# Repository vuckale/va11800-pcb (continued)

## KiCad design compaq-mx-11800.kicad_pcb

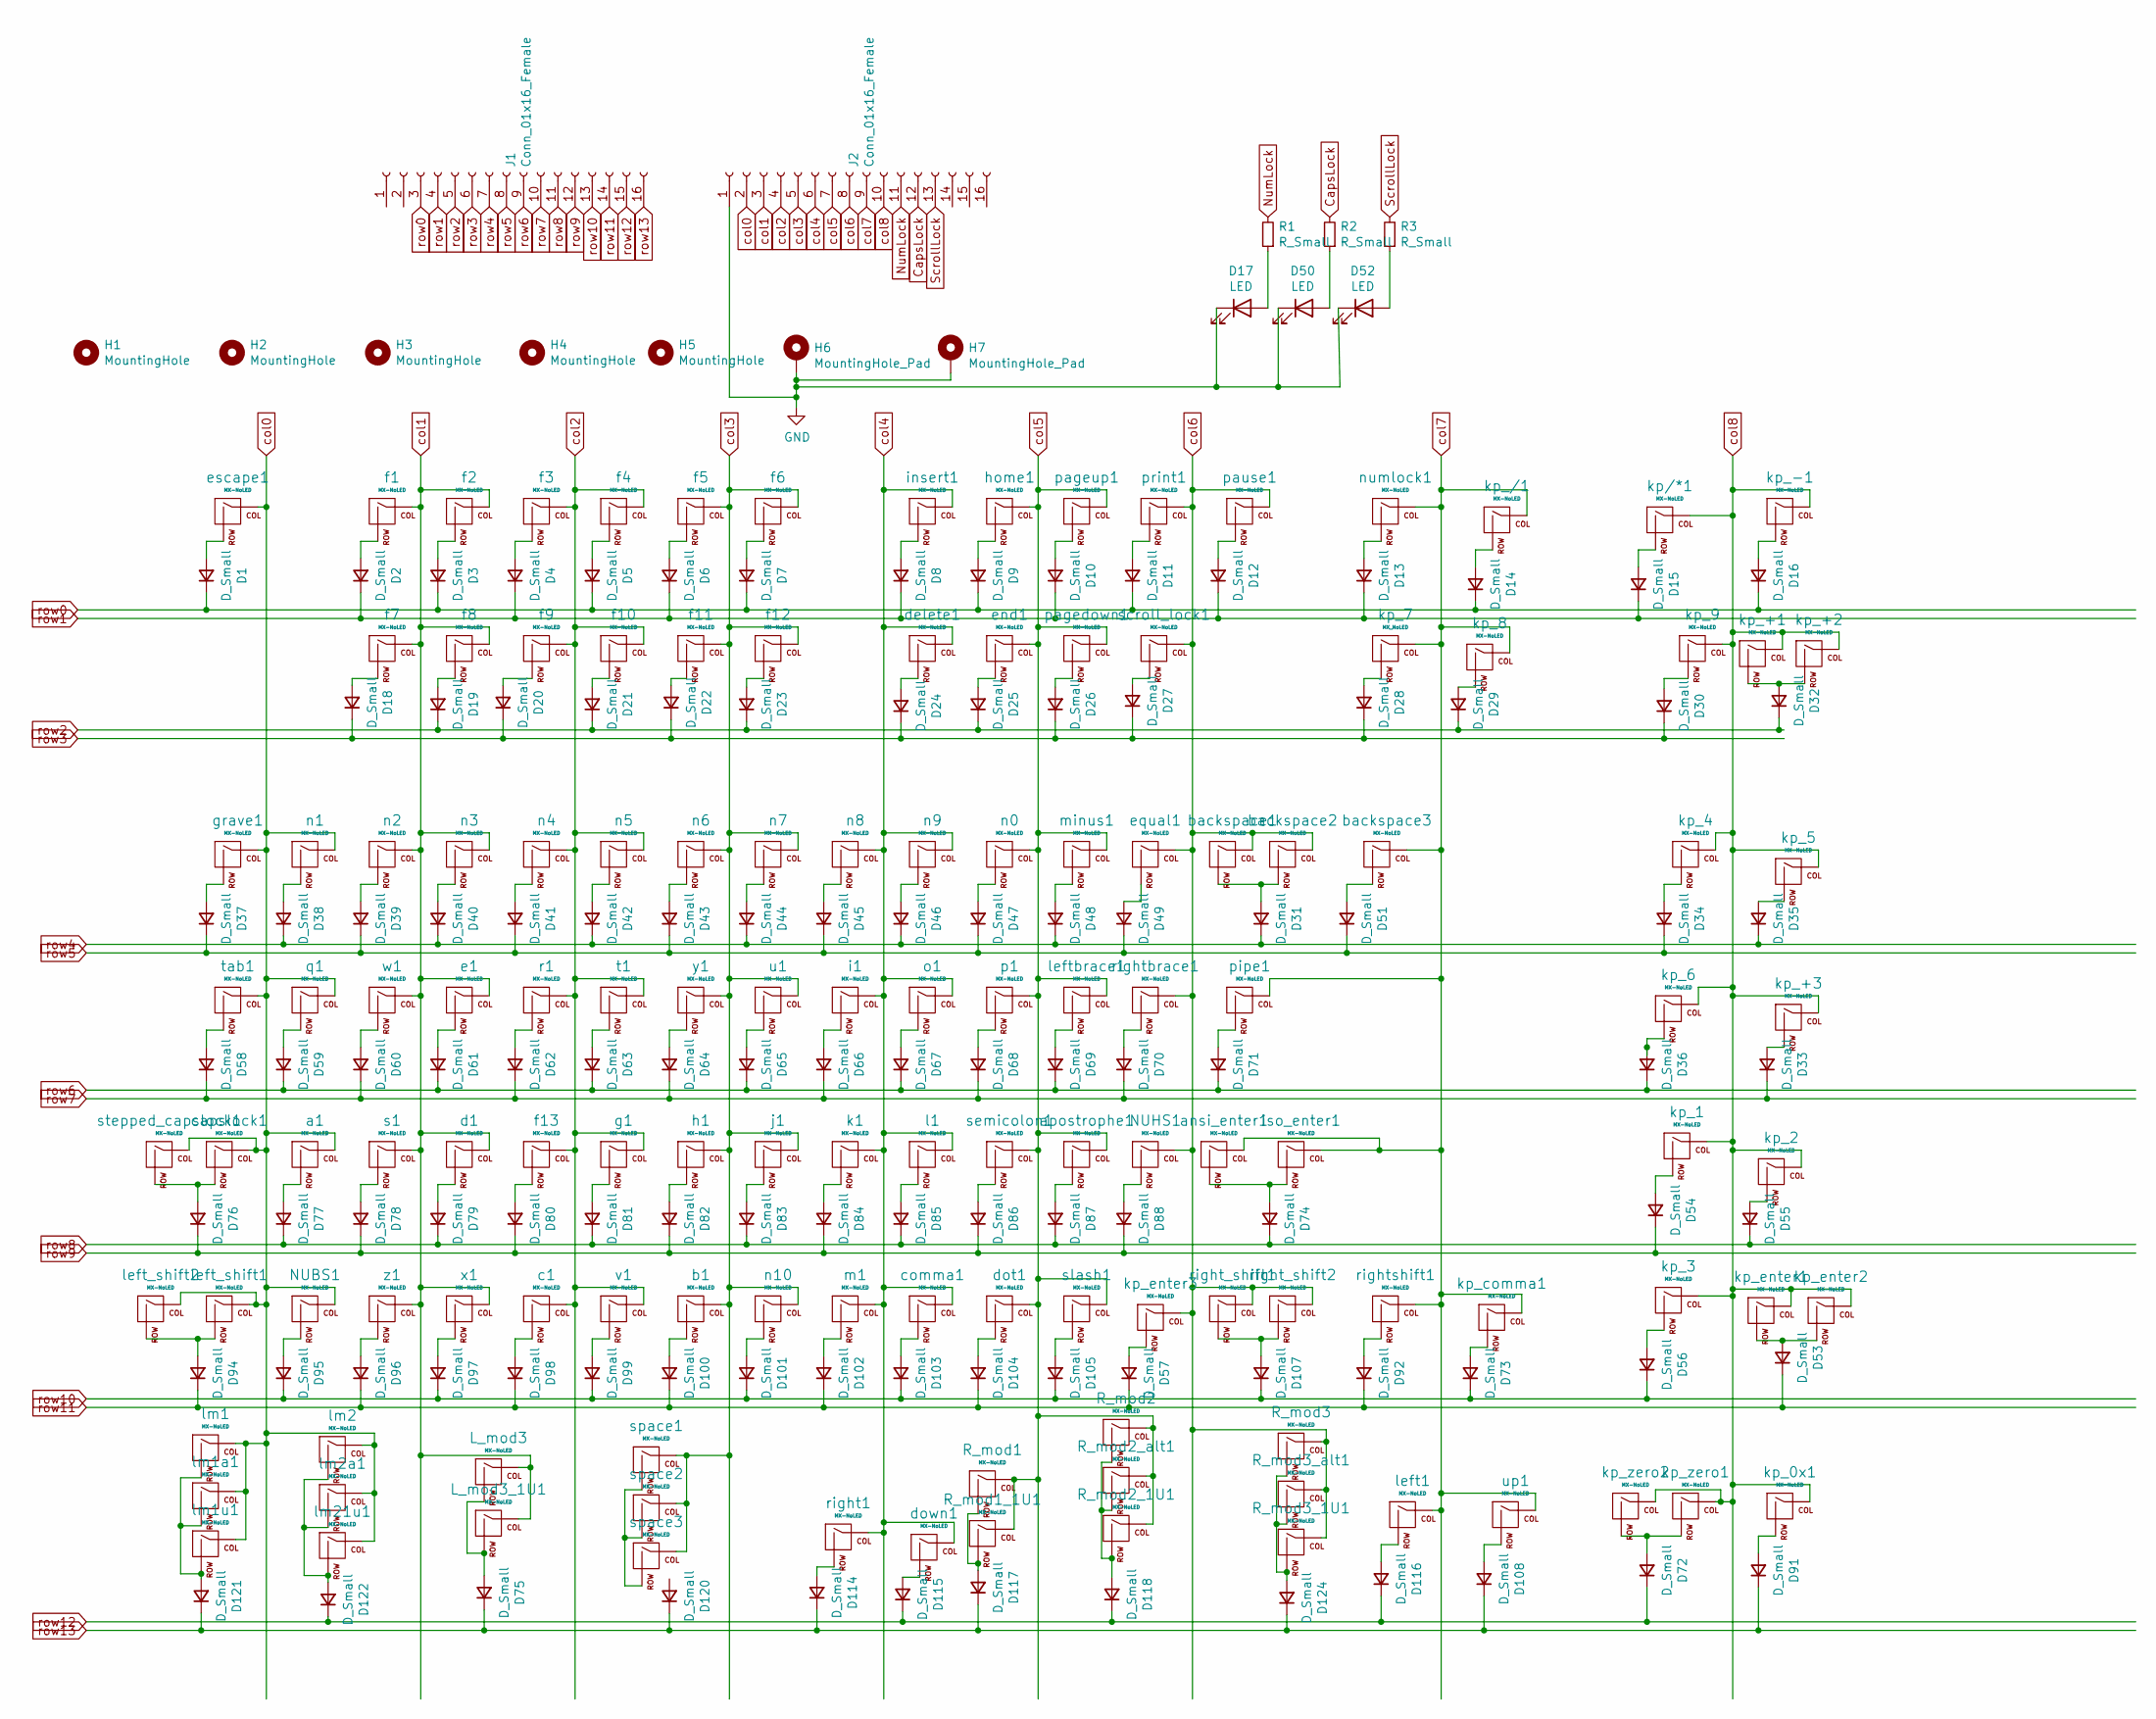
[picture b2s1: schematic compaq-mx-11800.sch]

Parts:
D1: D_Small; Diode-dual
D2, D3, D4, D5, D6, D7, D8, D9, D10, D11, D12, D13, D14, D15, D16, D18, D19, D20, D21, D22, D23, D24, D25, D26, D27, D28, D29, D30, D31, D32, D33, D34, D35, D36, D37, D38, D39, D40, D41, D42, D43, D44, D45, D46, D47, D48, D49, D51, D53, D54, D55, D56, D57, D58, D59, D60, D61, D62, D63, D64, D65, D66, D67, D68, D69, D70, D71, D72, D73, D74, D75, D76, D77, D78, D79, D80, D81, D82, D83, D84, D85, D86, D87, D88, D91, D92, D94, D95, D96, D97, D98, D99, D100, D101, D102, D103, D104, D105, D107, D108, D114, D115, D116, D117, D118, D120, D121, D122, D124: D_Small; Diode
D17, D50, D52: LED; LED_D2.00mm
H1, H2, H3, H4, H5: MountingHole; MountingHole_3.2mm_M3
H6, H7: MountingHole_Pad; SolidCopper
J1, J2: Conn_01x16_Female; PinHeader_1x16_P2.54mm_Vertical
L_mod3: MX-NoLED; MXOnly-1.25U-NoLED
L_mod3_1U1: MX-NoLED; MXOnly-1U-NoLED
NUBS1: MX-NoLED; MXOnly-1U-NoLED
NUHS1: MX-NoLED; MXOnly-1U-NoLED
R1, R2, R3: R_Small; Resistor
R_mod1, R_mod2_alt1, R_mod3_alt1: MX-NoLED; MXOnly-1.25U-NoLED
R_mod1_1U1, R_mod2_1U1, R_mod3_1U1: MX-NoLED; MXOnly-1U-NoLED
R_mod2, R_mod3: MX-NoLED; MXOnly-1.5U-NoLED
a1: MX-NoLED; MXOnly-1U-NoLED
ansi_enter1: MX-NoLED; MXOnly-2.25U-NoLED
apostrophe1: MX-NoLED; MXOnly-1U-NoLED
b1: MX-NoLED; MXOnly-1U-NoLED
backspace1, backspace3: MX-NoLED; MXOnly-1U-NoLED
backspace2: MX-NoLED; MXOnly-2U-ReversedStabilizers-NoLED
c1: MX-NoLED; MXOnly-1U-NoLED
capslock1: MX-NoLED; MXOnly-1.75U-NoLED
comma1: MX-NoLED; MXOnly-1U-NoLED
d1: MX-NoLED; MXOnly-1U-NoLED
delete1: MX-NoLED; MXOnly-1U-NoLED
dot1: MX-NoLED; MXOnly-1U-NoLED
down1: MX-NoLED; MXOnly-1U-NoLED
e1: MX-NoLED; MXOnly-1U-NoLED
end1: MX-NoLED; MXOnly-1U-NoLED
equal1: MX-NoLED; MXOnly-1U-NoLED
escape1: MX-NoLED; MXOnly-1U-NoLED
f1, f2, f3, f4, f5, f6, f7, f8, f9, f10, f11, f12, f13: MX-NoLED; MXOnly-1U-NoLED
g1: MX-NoLED; MXOnly-1U-NoLED
grave1: MX-NoLED; MXOnly-1U-NoLED
h1: MX-NoLED; MXOnly-1U-NoLED
home1: MX-NoLED; MXOnly-1U-NoLED
i1: MX-NoLED; MXOnly-1U-NoLED
insert1: MX-NoLED; MXOnly-1U-NoLED
iso_enter1: MX-NoLED; MXOnly-ISO-ReversedStabilizers-NoLED
j1: MX-NoLED; MXOnly-1U-NoLED
k1: MX-NoLED; MXOnly-1U-NoLED
kp/*1: MX-NoLED; MXOnly-1U-NoLED
kp_0x1, kp_1, kp_2, kp_3, kp_4, kp_5, kp_6, kp_8, kp_9: MX-NoLED; MXOnly-1U-NoLED
kp_7: MX_NoLED; MXOnly-1U-NoLED
kp_+1: MX-NoLED; MXOnly-2U-VerticalStabilizers-NoLED
kp_+2, kp_+3: MX-NoLED; MXOnly-1U-NoLED
kp_-1: MX-NoLED; MXOnly-1U-NoLED
kp_/1: MX-NoLED; MXOnly-1U-NoLED
kp_comma1: MX-NoLED; MXOnly-1U-NoLED
kp_enter1: MX-NoLED; MXOnly-2U-VerticalStabilizers-NoLED
kp_enter2, kp_enter3: MX-NoLED; MXOnly-1U-NoLED
kp_zero1: MX-NoLED; MXOnly-1U-NoLED
kp_zero2: MX-NoLED; MXOnly-2U-ReversedStabilizers-NoLED
l1: MX-NoLED; MXOnly-1U-NoLED
left1: MX-NoLED; MXOnly-1U-NoLED
left_shift1: MX-NoLED; MXOnly-2.25U-NoLED
left_shift2: MX-NoLED; MXOnly-1.25U-NoLED
leftbrace1: MX-NoLED; MXOnly-1U-NoLED
lm1, lm2: MX-NoLED; MXOnly-1.5U-NoLED
lm1a1, lm2a1: MX-NoLED; MXOnly-1.25U-NoLED
lm1u1, lm21u1: MX-NoLED; MXOnly-1U-NoLED
m1: MX-NoLED; MXOnly-1U-NoLED
minus1: MX-NoLED; MXOnly-1U-NoLED
n0, n1, n2, n3, n4, n5, n6, n7, n8, n9, n10: MX-NoLED; MXOnly-1U-NoLED
numlock1: MX-NoLED; MXOnly-1U-NoLED
o1: MX-NoLED; MXOnly-1U-NoLED
p1: MX-NoLED; MXOnly-1U-NoLED
pagedown1: MX-NoLED; MXOnly-1U-NoLED
pageup1: MX-NoLED; MXOnly-1U-NoLED
pause1: MX-NoLED; MXOnly-1U-NoLED
pipe1: MX-NoLED; MXOnly-1.5U-NoLED
print1: MX-NoLED; MXOnly-1U-NoLED
q1: MX-NoLED; MXOnly-1U-NoLED
r1: MX-NoLED; MXOnly-1U-NoLED
right1: MX-NoLED; MXOnly-1U-NoLED
right_shift1: MX-NoLED; MXOnly-1U-NoLED
right_shift2: MX-NoLED; MXOnly-2U-NoLED
rightbrace1: MX-NoLED; MXOnly-1U-NoLED
rightshift1: MX-NoLED; MXOnly-1U-NoLED
s1: MX-NoLED; MXOnly-1U-NoLED
scroll_lock1: MX-NoLED; MXOnly-1U-NoLED
semicolon1: MX-NoLED; MXOnly-1U-NoLED
slash1: MX-NoLED; MXOnly-1U-NoLED
space1: MX-NoLED; MXOnly-7U-NoLED
space2, space3: MX-NoLED; MXOnly-6.25U-NoLED
stepped_capslock1: MX-NoLED; MXOnly-1.25U-NoLED
t1: MX-NoLED; MXOnly-1U-NoLED
tab1: MX-NoLED; MXOnly-1.5U-NoLED
u1: MX-NoLED; MXOnly-1U-NoLED
up1: MX-NoLED; MXOnly-1U-NoLED
v1: MX-NoLED; MXOnly-1U-NoLED
w1: MX-NoLED; MXOnly-1U-NoLED
x1: MX-NoLED; MXOnly-1U-NoLED
y1: MX-NoLED; MXOnly-1U-NoLED
z1: MX-NoLED; MXOnly-1U-NoLED

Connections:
CapsLock: J2.12, R2.2
GND: D17.1 (K), D50.1 (K), D52.1 (K), H6.1, H7.1, J2.1
unnamed: D1.2 (A), escape1.2 (ROW)
unnamed: D2.2 (A), f1.2 (ROW)
unnamed: D3.2 (A), f2.2 (ROW)
unnamed: D4.2 (A), f3.2 (ROW)
unnamed: D5.2 (A), f4.2 (ROW)
unnamed: D6.2 (A), f5.2 (ROW)
unnamed: D7.2 (A), f6.2 (ROW)
unnamed: D8.2 (A), insert1.2 (ROW)
unnamed: D9.2 (A), home1.2 (ROW)
unnamed: D10.2 (A), pageup1.2 (ROW)
unnamed: D11.2 (A), print1.2 (ROW)
unnamed: D12.2 (A), pause1.2 (ROW)
unnamed: D13.2 (A), numlock1.2 (ROW)
unnamed: D14.2 (A), kp_/1.2 (ROW)
unnamed: D15.2 (A), kp/*1.2 (ROW)
unnamed: D16.2 (A), kp_-1.2 (ROW)
unnamed: D17.2 (A), R1.1
unnamed: D18.2 (A), f7.2 (ROW)
unnamed: D19.2 (A), f8.2 (ROW)
unnamed: D20.2 (A), f9.2 (ROW)
unnamed: D21.2 (A), f10.2 (ROW)
unnamed: D22.2 (A), f11.2 (ROW)
unnamed: D23.2 (A), f12.2 (ROW)
unnamed: D24.2 (A), delete1.2 (ROW)
unnamed: D25.2 (A), end1.2 (ROW)
unnamed: D26.2 (A), pagedown1.2 (ROW)
unnamed: D27.2 (A), scroll_lock1.2 (ROW)
unnamed: D28.2 (A), kp_7.2 (ROW)
unnamed: D29.2 (A), kp_8.2 (ROW)
unnamed: D30.2 (A), kp_9.2 (ROW)
unnamed: D31.2 (A), backspace1.2 (ROW), backspace2.2 (ROW)
unnamed: D32.2 (A), kp_+1.2 (ROW), kp_+2.2 (ROW)
unnamed: D33.2 (A), kp_+3.2 (ROW)
unnamed: D34.2 (A), kp_4.2 (ROW)
unnamed: D35.2 (A), kp_5.2 (ROW)
unnamed: D36.2 (A), kp_6.2 (ROW)
unnamed: D37.2 (A), grave1.2 (ROW)
unnamed: D38.2 (A), n1.2 (ROW)
unnamed: D39.2 (A), n2.2 (ROW)
unnamed: D40.2 (A), n3.2 (ROW)
unnamed: D41.2 (A), n4.2 (ROW)
unnamed: D42.2 (A), n5.2 (ROW)
unnamed: D43.2 (A), n6.2 (ROW)
unnamed: D44.2 (A), n7.2 (ROW)
unnamed: D45.2 (A), n8.2 (ROW)
unnamed: D46.2 (A), n9.2 (ROW)
unnamed: D47.2 (A), n0.2 (ROW)
unnamed: D48.2 (A), minus1.2 (ROW)
unnamed: D49.2 (A), equal1.2 (ROW)
unnamed: D50.2 (A), R2.1
unnamed: D51.2 (A), backspace3.2 (ROW)
unnamed: D52.2 (A), R3.1
unnamed: D53.2 (A), kp_enter1.2 (ROW), kp_enter2.2 (ROW)
unnamed: D54.2 (A), kp_1.2 (ROW)
unnamed: D55.2 (A), kp_2.2 (ROW)
unnamed: D56.2 (A), kp_3.2 (ROW)
unnamed: D57.2 (A), kp_enter3.2 (ROW)
unnamed: D58.2 (A), tab1.2 (ROW)
unnamed: D59.2 (A), q1.2 (ROW)
unnamed: D60.2 (A), w1.2 (ROW)
unnamed: D61.2 (A), e1.2 (ROW)
unnamed: D62.2 (A), r1.2 (ROW)
unnamed: D63.2 (A), t1.2 (ROW)
unnamed: D64.2 (A), y1.2 (ROW)
unnamed: D65.2 (A), u1.2 (ROW)
unnamed: D66.2 (A), i1.2 (ROW)
unnamed: D67.2 (A), o1.2 (ROW)
unnamed: D68.2 (A), p1.2 (ROW)
unnamed: D69.2 (A), leftbrace1.2 (ROW)
unnamed: D70.2 (A), rightbrace1.2 (ROW)
unnamed: D71.2 (A), pipe1.2 (ROW)
unnamed: D72.2 (A), kp_zero1.2 (ROW), kp_zero2.2 (ROW)
unnamed: D73.2 (A), kp_comma1.2 (ROW)
unnamed: D74.2 (A), ansi_enter1.2 (ROW), iso_enter1.2 (ROW)
unnamed: D75.2 (A), L_mod3.2 (ROW), L_mod3_1U1.2 (ROW)
unnamed: D76.2 (A), capslock1.2 (ROW), stepped_capslock1.2 (ROW)
unnamed: D77.2 (A), a1.2 (ROW)
unnamed: D78.2 (A), s1.2 (ROW)
unnamed: D79.2 (A), d1.2 (ROW)
unnamed: D80.2 (A), f13.2 (ROW)
unnamed: D81.2 (A), g1.2 (ROW)
unnamed: D82.2 (A), h1.2 (ROW)
unnamed: D83.2 (A), j1.2 (ROW)
unnamed: D84.2 (A), k1.2 (ROW)
unnamed: D85.2 (A), l1.2 (ROW)
unnamed: D86.2 (A), semicolon1.2 (ROW)
unnamed: D87.2 (A), apostrophe1.2 (ROW)
unnamed: D88.2 (A), NUHS1.2 (ROW)
unnamed: D91.2 (A), kp_0x1.2 (ROW)
unnamed: D92.2 (A), rightshift1.2 (ROW)
unnamed: D94.2 (A), left_shift1.2 (ROW), left_shift2.2 (ROW)
unnamed: D95.2 (A), NUBS1.2 (ROW)
unnamed: D96.2 (A), z1.2 (ROW)
unnamed: D97.2 (A), x1.2 (ROW)
unnamed: D98.2 (A), c1.2 (ROW)
unnamed: D99.2 (A), v1.2 (ROW)
unnamed: D100.2 (A), b1.2 (ROW)
unnamed: D101.2 (A), n10.2 (ROW)
unnamed: D102.2 (A), m1.2 (ROW)
unnamed: D103.2 (A), comma1.2 (ROW)
unnamed: D104.2 (A), dot1.2 (ROW)
unnamed: D105.2 (A), slash1.2 (ROW)
unnamed: D107.2 (A), right_shift1.2 (ROW), right_shift2.2 (ROW)
unnamed: D108.2 (A), up1.2 (ROW)
unnamed: D114.2 (A), right1.2 (ROW)
unnamed: D115.2 (A), down1.2 (ROW)
unnamed: D116.2 (A), left1.2 (ROW)
unnamed: D117.2 (A), R_mod1.2 (ROW), R_mod1_1U1.2 (ROW)
unnamed: D118.2 (A), R_mod2.2 (ROW), R_mod2_1U1.2 (ROW), R_mod2_alt1.2 (ROW)
unnamed: D121.2 (A), lm1.2 (ROW), lm1a1.2 (ROW), lm1u1.2 (ROW)
unnamed: D122.2 (A), lm2.2 (ROW), lm2a1.2 (ROW), lm21u1.2 (ROW)
unnamed: D124.2 (A), R_mod3.2 (ROW), R_mod3_1U1.2 (ROW), R_mod3_alt1.2 (ROW)
unnamed: space1.2 (ROW), space2.2 (ROW), space3.2 (ROW)
NumLock: J2.11, R1.2
ScrollLock: J2.13, R3.2
col0: J2.2, NUBS1.1 (COL), a1.1 (COL), capslock1.1 (COL), escape1.1 (COL), grave1.1 (COL), left_shift1.1 (COL), left_shift2.1 (COL), lm1.1 (COL), lm1a1.1 (COL), lm1u1.1 (COL), lm2.1 (COL), lm2a1.1 (COL), lm21u1.1 (COL), n1.1 (COL), q1.1 (COL), stepped_capslock1.1 (COL), tab1.1 (COL)
col1: J2.3, L_mod3.1 (COL), L_mod3_1U1.1 (COL), d1.1 (COL), e1.1 (COL), f1.1 (COL), f2.1 (COL), f7.1 (COL), f8.1 (COL), n2.1 (COL), n3.1 (COL), s1.1 (COL), w1.1 (COL), x1.1 (COL), z1.1 (COL)
col2: J2.4, c1.1 (COL), f3.1 (COL), f4.1 (COL), f9.1 (COL), f10.1 (COL), f13.1 (COL), g1.1 (COL), n4.1 (COL), n5.1 (COL), r1.1 (COL), t1.1 (COL), v1.1 (COL)
col3: J2.5, b1.1 (COL), f5.1 (COL), f6.1 (COL), f11.1 (COL), f12.1 (COL), h1.1 (COL), j1.1 (COL), n6.1 (COL), n7.1 (COL), n10.1 (COL), space1.1 (COL), space2.1 (COL), space3.1 (COL), u1.1 (COL), y1.1 (COL)
col4: J2.6, comma1.1 (COL), delete1.1 (COL), down1.1 (COL), i1.1 (COL), insert1.1 (COL), k1.1 (COL), l1.1 (COL), m1.1 (COL), n8.1 (COL), n9.1 (COL), o1.1 (COL), right1.1 (COL)
col5: J2.7, R_mod1.1 (COL), R_mod1_1U1.1 (COL), R_mod2.1 (COL), R_mod2_1U1.1 (COL), R_mod2_alt1.1 (COL), apostrophe1.1 (COL), dot1.1 (COL), end1.1 (COL), home1.1 (COL), leftbrace1.1 (COL), minus1.1 (COL), n0.1 (COL), p1.1 (COL), pagedown1.1 (COL), pageup1.1 (COL), semicolon1.1 (COL), slash1.1 (COL)
col6: J2.8, NUHS1.1 (COL), R_mod3.1 (COL), R_mod3_1U1.1 (COL), R_mod3_alt1.1 (COL), backspace1.1 (COL), backspace2.1 (COL), equal1.1 (COL), kp_enter3.1 (COL), pause1.1 (COL), print1.1 (COL), right_shift1.1 (COL), right_shift2.1 (COL), rightbrace1.1 (COL), scroll_lock1.1 (COL)
col7: J2.9, ansi_enter1.1 (COL), backspace3.1 (COL), iso_enter1.1 (COL), kp_7.1 (COL), kp_8.1 (COL), kp_/1.1 (COL), kp_comma1.1 (COL), left1.1 (COL), numlock1.1 (COL), pipe1.1 (COL), rightshift1.1 (COL), up1.1 (COL)
col8: J2.10, kp/*1.1 (COL), kp_0x1.1 (COL), kp_1.1 (COL), kp_2.1 (COL), kp_3.1 (COL), kp_4.1 (COL), kp_5.1 (COL), kp_6.1 (COL), kp_9.1 (COL), kp_+1.1 (COL), kp_+2.1 (COL), kp_+3.1 (COL), kp_-1.1 (COL), kp_enter1.1 (COL), kp_enter2.1 (COL), kp_zero1.1 (COL), kp_zero2.1 (COL)
row0: D1.1 (K), D3.1 (K), D5.1 (K), D7.1 (K), D9.1 (K), D11.1 (K), D14.1 (K), D16.1 (K), J1.3
row1: D2.1 (K), D4.1 (K), D6.1 (K), D8.1 (K), D10.1 (K), D12.1 (K), D13.1 (K), D15.1 (K), J1.4
row2: D19.1 (K), D21.1 (K), D23.1 (K), D25.1 (K), D29.1 (K), D32.1 (K), J1.5
row3: D18.1 (K), D20.1 (K), D22.1 (K), D24.1 (K), D26.1 (K), D27.1 (K), D28.1 (K), D30.1 (K), J1.6
row4: D31.1 (K), D35.1 (K), D38.1 (K), D40.1 (K), D42.1 (K), D44.1 (K), D46.1 (K), D48.1 (K), J1.7
row5: D34.1 (K), D37.1 (K), D39.1 (K), D41.1 (K), D43.1 (K), D45.1 (K), D47.1 (K), D49.1 (K), D51.1 (K), J1.8
row6: D36.1 (K), D59.1 (K), D61.1 (K), D63.1 (K), D65.1 (K), D67.1 (K), D69.1 (K), D71.1 (K), J1.9
row7: D33.1 (K), D58.1 (K), D60.1 (K), D62.1 (K), D64.1 (K), D66.1 (K), D68.1 (K), D70.1 (K), J1.10
row8: D55.1 (K), D74.1 (K), D77.1 (K), D79.1 (K), D81.1 (K), D83.1 (K), D85.1 (K), D87.1 (K), J1.11
row9: D54.1 (K), D76.1 (K), D78.1 (K), D80.1 (K), D82.1 (K), D84.1 (K), D86.1 (K), D88.1 (K), J1.12
row10: D56.1 (K), D73.1 (K), D95.1 (K), D97.1 (K), D99.1 (K), D101.1 (K), D103.1 (K), D105.1 (K), D107.1 (K), J1.13
row11: D53.1 (K), D57.1 (K), D92.1 (K), D94.1 (K), D96.1 (K), D98.1 (K), D100.1 (K), D102.1 (K), D104.1 (K), J1.14
row12: D72.1 (K), D115.1 (K), D116.1 (K), D118.1 (K), D122.1 (K), J1.15
row13: D75.1 (K), D91.1 (K), D108.1 (K), D114.1 (K), D117.1 (K), D120.1 (K), D121.1 (K), D124.1 (K), J1.16

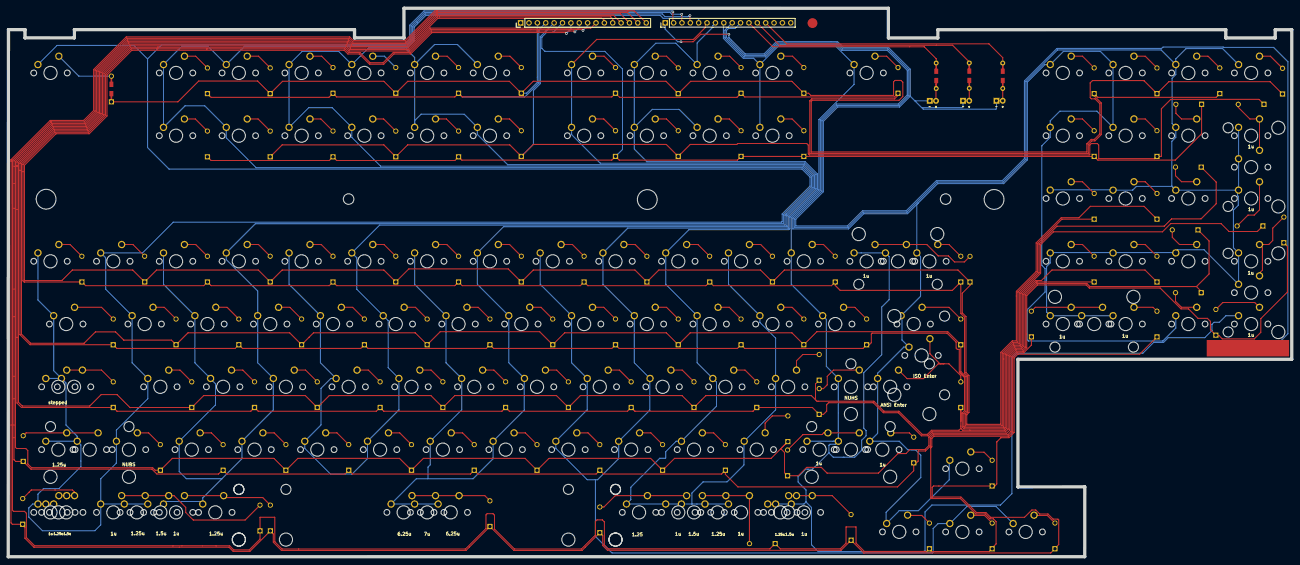
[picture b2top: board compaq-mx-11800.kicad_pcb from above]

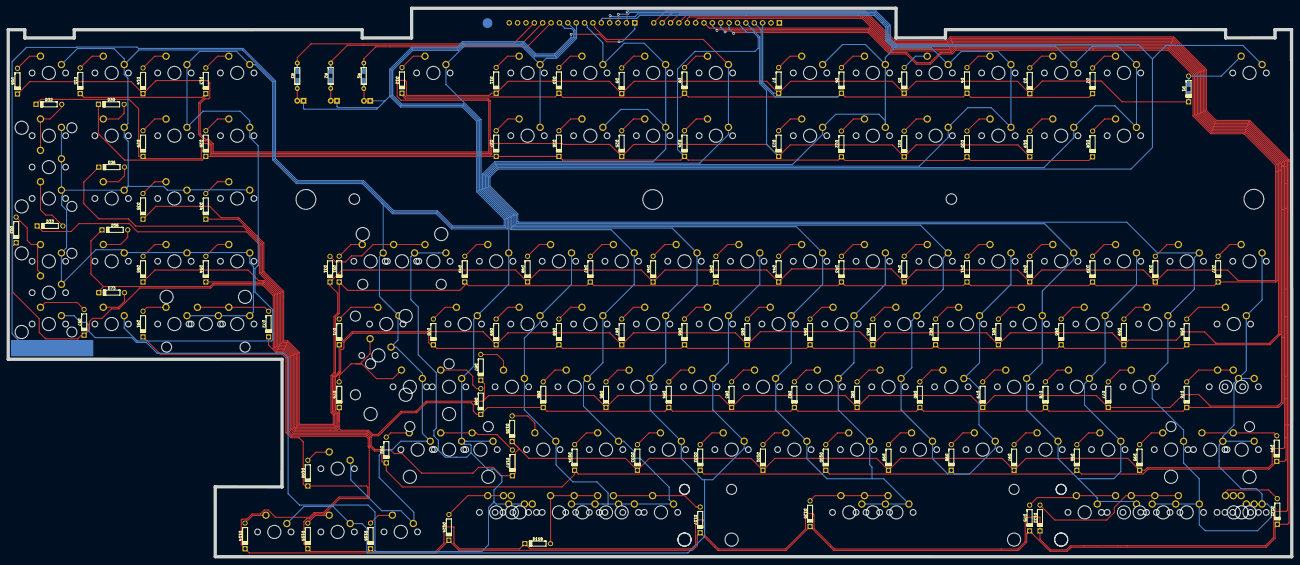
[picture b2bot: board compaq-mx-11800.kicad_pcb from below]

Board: 2 copper layers, 389.5 x 166.4 mm, 255 parts (119 on the bottom side), 140 nets.

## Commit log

2021-12-21 add submodules
2021-12-21 add base layout with diodes
2021-12-21 correct row and column placement on pcb
2021-12-22 draw board outline
2021-12-22 adjust arrow cluster spacing
2021-12-22 readjust pcb size and 2 mounting holes
2021-12-23 add rest of the pcb mounting holes
2021-12-23 remove extra diodes for multilayout
2021-12-23 correct diode placement and orientation
2021-12-23 connect numpad diodes
2021-12-23 connect diodes - frow
2021-12-23 connect diodes for frow
2021-12-24 connect rows and columns in .sch
2021-12-24 rewire numpad in .sch
2021-12-24 connect the traces - numpad
2021-12-25 fix multilayout column pin connections
2022-01-05 connect numpad to existing rows and columns
2022-01-05 route column traces to top
2022-01-05 route row traces to top
2022-01-05 modify column traces
2022-01-06 traces cleanup
2022-01-07 trace correction
2022-01-07 connect rows to output pins
2022-01-07 fix some traces and stabilizer holes
2022-01-07 reorder col and row pins
2022-01-07 cleanup .sch
2022-01-08 add filled zones
2022-01-09 add ground pins
2022-01-10 add rest of the filled zones
2022-01-10 readjust mounting hole positions
2022-01-10 add footprint for 3mm diode and add footprints to pcb
2022-01-12 mark bottom row and iso enter + align led diodes
2022-01-16 reorder keys and remove 1 column
2022-01-18 add polarity markings for LEDS
2022-02-02 modify bottom row
2022-02-02 reorder columns and rows in schema and pcb to be in order
2022-02-03 revert to using MX_only
2022-02-04 remove solder mask from front pcb traces
2022-02-04 update diode footprint
2022-02-04 add 1u-1u-1u-7u-1u-1u-1u support for bottom row
2022-02-04 remove solder from traces on back PCB
2022-02-05 fix scematic row col order
2022-02-05 clean up schematics
2022-02-05 add silk for alternate layouts
2022-02-05 connect wires for LEDs
2022-02-05 cleanup
2022-02-06 route GND to different pin
2022-02-06 add resistor pads to LEDs
2022-02-09 rename project and small silkscreen adjustments
2022-02-09 fix footprint associations
2022-02-10 add github repository silkscreen
2022-02-10 add silkscreen on traces
2022-02-10 small logo adjustments
2022-02-11 add missing letter "u" for bottom row
2022-02-13 add Gerber files
2022-02-13 small adjustments
2022-02-17 modify GND pad
2022-02-17 remove submodule
2022-02-17 add docs
2022-02-17 add README and remove submodule
2022-02-17 fix image URL
2022-02-17 modify footprint and library preferences
2022-08-30 corrected switch placement
2022-08-30 remove front and back silkscreen and front mask from switch pads
2022-08-31 reconect disconnected tracks
2022-08-31 correct traces and mounting holes
2022-10-11 fix encoder placement and add 6u spacebar support
2022-10-11 add matrix png in docs
2022-10-11 add .gitignore
2022-10-15 fix pads on switch footprint
2022-10-18 cleanup traces
2022-10-19 fix ground for encoder and reset switch and trace cleanup
2022-10-19 add GND filled zone
2022-10-19 add silkscreen for encoders and modify bottom row stabilizer silkscreen
2022-10-19 fix GND and RST vias spacing
2022-10-19 add GND and RST silkscreen on the back and move github repository url
2022-10-21 add oshw logo and minor adjustments
2022-10-21 move submodules
2022-10-21 cleanup libraries
2022-10-21 cleanup kicad_sch
2022-10-22 rename symbols in .kicad_sch
2022-10-22 fix excess traces on alpha keys
